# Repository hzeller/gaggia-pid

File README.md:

PID controller for Gaggia Classic
=================================

# Temperature Sensor
Using the [Max31725] for nice high accuracy and fast temperature updates. Also
a bit overengineered, but that is what I had lying around.

The sensor is on a little PCB (which you find in the
[sensor-mount/](./sensor-mount) directory. Glued into the existing brass
screw-cups the original bimetallic sensor was in (using JB Weld, which is
a sufficiently high-temperature epoxy), then wired up with silicone wiring and
sealed with silicone.

Mount on the side of the boiler where the original brew temp sensor was.

PCB            | Preparing mount | Glued in cup | Sealed
---------------|-----------------|--------------|--------
 |  |  | 

# PID Controller

Runs on a conventional Arduino Nano.

To program, get avr-gcc and avrdude. The Makefile takes care of compiling
and flashing:

```
cd firmware
make flash
```

The sytem is powered with a sealed 5V power supply CUI PSK-3D-5.
The Solid State Relay is a Panasonic AQJ112V.

The USB connector is arranged in a way that it is reachable through one of the
opening on the back. From the front, the machine is entirely unaltered (unlike
many of the somewhat ugly PID mods of this machine).

You connect with a serial console to the PID controller, adjust
PID parameters and watch an ASCII-art 'graphical' output of the temperature
sensor (see the picture with the Laptop in view and the rising temperature
displayed).

PID parameters can be tuned with the interface presented on the serial
interface and stored in EEPROM.

Serial interface running by default on 38400 bps:

```bash
tio -b 38400 /dev/ttyUSB0
```

Menu:
```
#            ☕ Gaggia PID controller
#(c) 2021 Henner Zeller  |  GNU Public License
#Commands
#       l - Start log to console. Stop with any key.
#       L - Ditto. With 'graph'
#       n - Now. Print PID parameters, last temp and control out.
#
#       s <setpoint> - set setpoint.
#       p <Kp>       - set proportional gain.
#       i <Ki>       - set integral gain.
#       d <Kd>       - set derivative gain.
#
#       w - Write PID parameters to EEPROM.
#       r - Restore PID parameters from EEPROM.
#       h - This help
```

Components         | Mounted | Back  | Settings via USB
-------------------|---------|-------|--------------------------
 |  |  | 

[Max31725]: https://datasheets.maximintegrated.com/en/ds/MAX31725-MAX31726.pdf

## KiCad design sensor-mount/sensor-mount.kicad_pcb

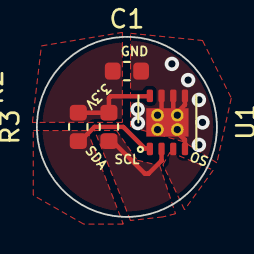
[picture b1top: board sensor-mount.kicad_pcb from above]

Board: 2 copper layers, 10.0 x 10.0 mm, 4 parts (0 on the bottom side), 4 nets.

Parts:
C1: 220n; C_0603_1608Metric
R2, R3: 4k7; R_0603_1608Metric
U1: MAX31725; DFN-8-1EP_3x3mm_P0.65mm_EP1.7x2.05mm

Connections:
/SCL: R2.2, U1.2 (SCL)
/SDA: R3.2, U1.1 (SDA)
GND: C1.2, U1.4 (GND), U1.5 (A2), U1.6 (A1), U1.7 (A0), U1.9 (EP)
VCC: C1.1, R2.1, R3.1, U1.8 (VDD)

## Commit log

2021-03-07 Initial version.
2021-03-07 The Maxim footprint has 0.65mm pitch.
2021-03-12 Start firmware. For now, just read temperature from MAX31725 and display.
    * Regularly read temperature sensor (using a timer interrupt).
    * Provide a simple serial interface to query temperature and
    output a log with an character 'graph'.
    * Show current temperature on a SH1106 display.
    * No PID calculation or output yet.
    Temperature sensor and SH1106 are connected to the same i2c bus.
2022-03-06 Remove display support; not needed in the final machine.
2022-03-07 Add low-speed PWM to switch heater.
2022-03-09 Switch to float to represent real values.
    Easier to handle than fixed point. Since we have enough program
    flash capacity and do very little calculations, this is doable.
2022-03-11 Provide editing of values (setpoint, Kp, Ki, Kd). Store in EEPROM.
2022-03-11 Provide documentation for 'n'ow command.
2022-03-11 Since we have backspace-editing now, count chars in buf not read().
2022-03-11 Editing: beep when line too long.
2022-03-11 Prevent setting invalid values.
2022-03-12 Display removed, font not needed anymore.
2022-03-12 Move PID and serial utility functions into their own files.
2022-03-14 Improve anti-windup.
    Stop integrating if we are already clamping the output and integration
    would contribute to more output overshoot that we have to decay later.
2022-03-14 Higher resolution for the heater PWM (32 vs. 16 levels).
2022-04-03 Add README.
2022-05-22 Not using display anymore, bdfont-support.{h,cc} not needed.
2022-08-14 Make it simpler to use in nix, provide all dependencies.
2022-08-14 Upgrade to latest kicad; fix missing symbol library config.
2022-08-14 Choose compiler that produces smallest code.
2022-08-14 Fix path to 3D models.
2022-11-20 Tweak compile, link options: slightly smaller final binary.
2024-01-13 Document default serial speed.
2025-03-08 Update gcc dep.
2026-02-28 Remove obsolete compiler.
2026-02-28 Update kicad outputs to latest
2026-02-28 Exclude local kicad stuff in gitignore
